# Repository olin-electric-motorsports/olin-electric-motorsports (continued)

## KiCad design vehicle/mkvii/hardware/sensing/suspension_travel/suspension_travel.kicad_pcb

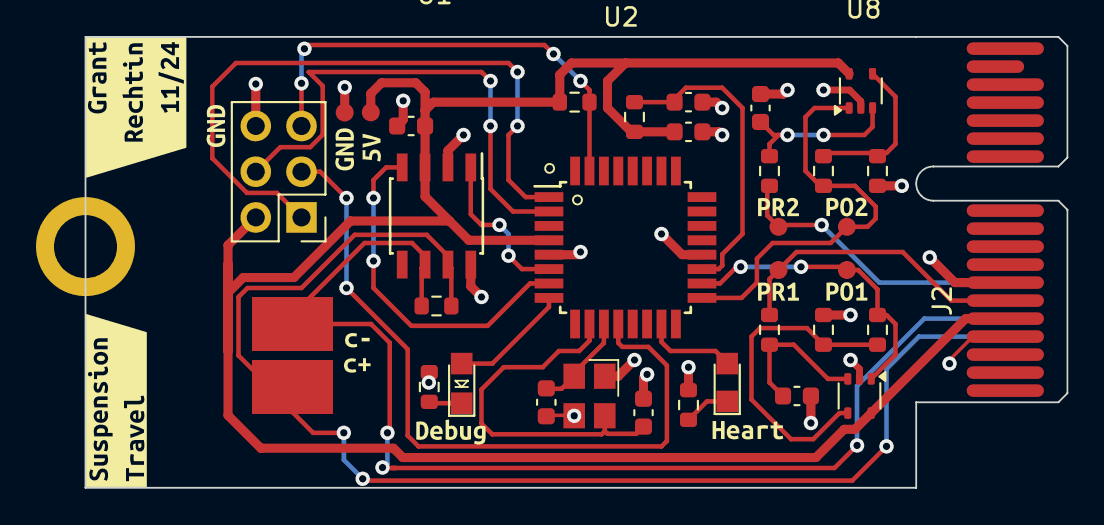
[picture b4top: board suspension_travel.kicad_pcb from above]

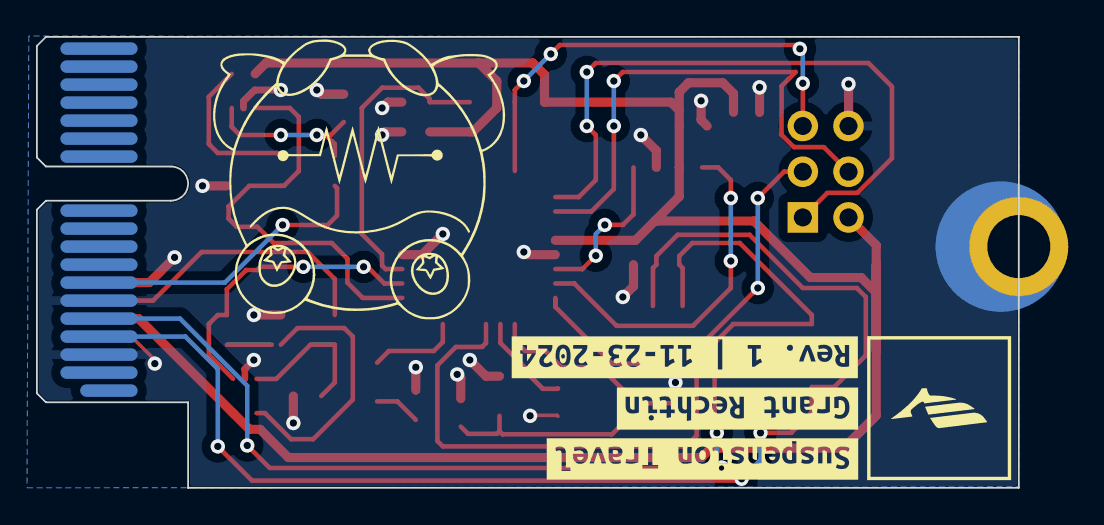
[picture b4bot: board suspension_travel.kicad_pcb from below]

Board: 2 copper layers, 54.6 x 25.0 mm, 52 parts (3 on the bottom side), 25 nets.

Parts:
5VTestPoint1: TestPoint; TestPoint_Pad_D1mm
C1, C3, C6, C7: C_0.1uF; C_0603
C2: C_100pF; C_0603
C4, C5: C_30pF; C_0603
Can+Tp1: TestPoint; Test_Point_SMD
Can-TP1: TestPoint; Test_Point_SMD
D1: LED_0805; LED_0805_OEM
D2: LED_AMBER; CHIPLED_0805
GND1: TestPoint; TestPoint_Pad_D1mm
H1: CONN_MountingHole; PCIe_Mount
J1: CONN_02X03; PinHeader_2x03_P2.54mm_Vertical
J2: CONN_pcie_x1; pcie_x1
LP1_POST1, LP1_PRE1, LP2_POST1, LP2_PRE1: TestPoint; TestPoint_Pad_D1mm
R1, R4, R5, R6, R9, R10: R_100; R_0603
R2: R_120_DNP; R_0603
R3: R_10K; R_0603
R7, R8: R_200; R_0603
R11: R_1K; R_0603
U1: MCP2561-E_SN; SOIC-8_3.9x4.9mm_Pitch1.27mm_OEM
U2: ATMEGA16M1; TQFP-32_7x7mm_Pitch0.8mm
U3, U8: U_OPAMP_MCP6001; SOT-353_SC-70-5
Y1: Crystal_SMD; Crystal_TXC7M
kibuzzard-673FD6A4: G***; kibuzzard-673FD6A4
kibuzzard-673FD6B3: G***; kibuzzard-673FD6B3
kibuzzard-673FD6DC: G***; kibuzzard-673FD6DC
kibuzzard-673FD6EA: G***; kibuzzard-673FD6EA
kibuzzard-673FD6F4: G***; kibuzzard-673FD6F4
kibuzzard-673FD70C: G***; kibuzzard-673FD70C
kibuzzard-673FD675, kibuzzard-673FD675#2: G***; kibuzzard-673FD675
kibuzzard-673FD704: G***; kibuzzard-673FD704
kibuzzard-673FD725: G***; kibuzzard-673FD725
kibuzzard-673FD744: G***; kibuzzard-673FD744
kibuzzard-6740EEA9: G***; kibuzzard-6740EEA9
kibuzzard-6740EF04: G***; kibuzzard-6740EF04
kibuzzard-674242B4: G***; kibuzzard-674242B4
kibuzzard-67424246: G***; kibuzzard-67424246
kibuzzard-67424290: G***; kibuzzard-67424290

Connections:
+5V: 5VTestPoint1.1, C1.1, C3.1, J1.2, J2.B5 (5V), R1.1, R3.1, U1.3 (VDD), U2.4 (VCC), U3.5 (V+), U8.5 (V+)
/CAN_+: Can+Tp1.1, J2.A4 (CAN+), R2.1, U1.7 (CANH)
/CAN_-: Can-TP1.1, J2.A5 (CAN-), R2.2, U1.6 (CANL)
/CAN_RX: U1.4 (RXD), U2.7 ((PCINT11/T1/ICP1B/RXCAN)PC3)
/CAN_TX: U1.1 (TXD), U2.6 ((PCINT10/T0/TXCAN)PC2)
/DEBUG_LED: D1.2 (A), U2.8 ((PCINT0/MISO/PSCOUT2A)PB0)
/Heartbeat: D2.2 (A), U2.15 ((PCINT23/ACMP0)PD7)
/MISO: J1.1, U2.1 ((PCINT18/PSCIN2/OC1A/MISO_A)PD2)
/MOSI: J1.4, U2.2 ((PCINT19/TXD/TXLIN/OC0A/~SS/MOSI_A)PD3)
/RESET: J1.5, R3.2, U2.31 ((PCINT24/OCD/~RESET)PE0)
/SCK: J1.3, U2.12 ((PCINT20/ADC1/RXD/RXLIN/ICP1A/SCK_A)PD4)
/lp1_Vout: J2.B6 (io_1), LP1_PRE1.1, R5.1
/lp1_fVout: LP1_POST1.1, R9.1, U2.18 ((PCINT13/ADC9/ACMP3/AMP1+)PC5), U3.1
/lp2_Vout: J2.A7 (io_2), LP2_PRE1.1, R6.1
/lp2_fVout: LP2_POST1.1, R10.1, U2.17 ((PCINT12/ADC8/ACMPN3/AMP1-)PC4), U8.1
GND: C1.2, C2.2, C3.2, C4.2, C5.2, C6.2, C7.2, GND1.1, H1.1, J1.6, J2.A3 (GND), J2.A6 (io_0), J2.B4 (GND), J2.B7 (io_3), R4.2, R7.1, R8.1, R11.2, U1.2 (VSS), U1.8 (STBY), U2.5 (GND), U2.20 (AGND), U3.2 (V-), U8.2 (V-), Y1.2, Y1.4
unnamed: D1.1 (K), R4.1
unnamed: D2.1 (K), R11.1
unnamed: C5.1, U2.10 ((PCINT25/OC0B/XTAL1)PE1), Y1.3
unnamed: C4.1, U2.11 ((PCINT26/ADC0/XTAL2)PE2), Y1.1
unnamed: C2.1, R1.2, U2.19 (AVCC)
unnamed: C6.1, R5.2, U3.3 (+)
unnamed: R7.2, R9.2, U3.4 (-)
unnamed: C7.1, R6.2, U8.3 (+)
unnamed: R8.2, R10.2, U8.4 (-)

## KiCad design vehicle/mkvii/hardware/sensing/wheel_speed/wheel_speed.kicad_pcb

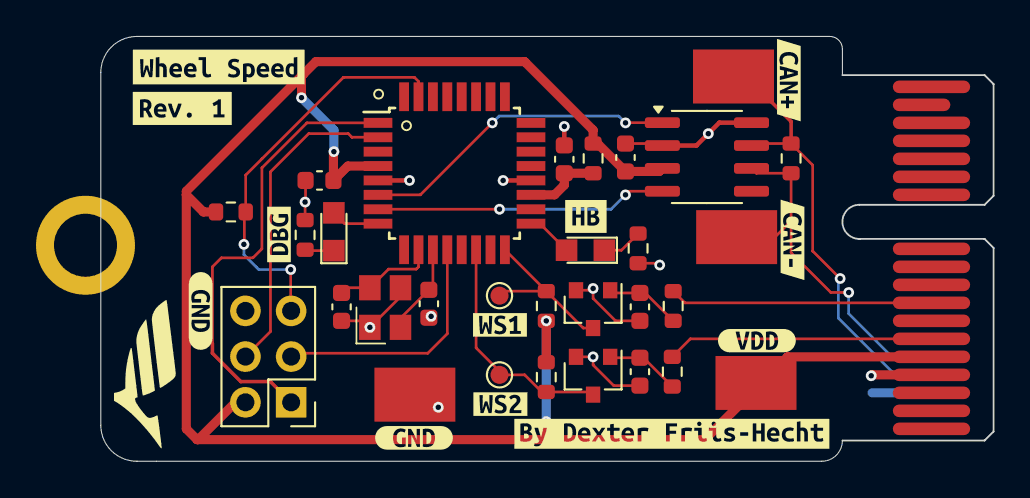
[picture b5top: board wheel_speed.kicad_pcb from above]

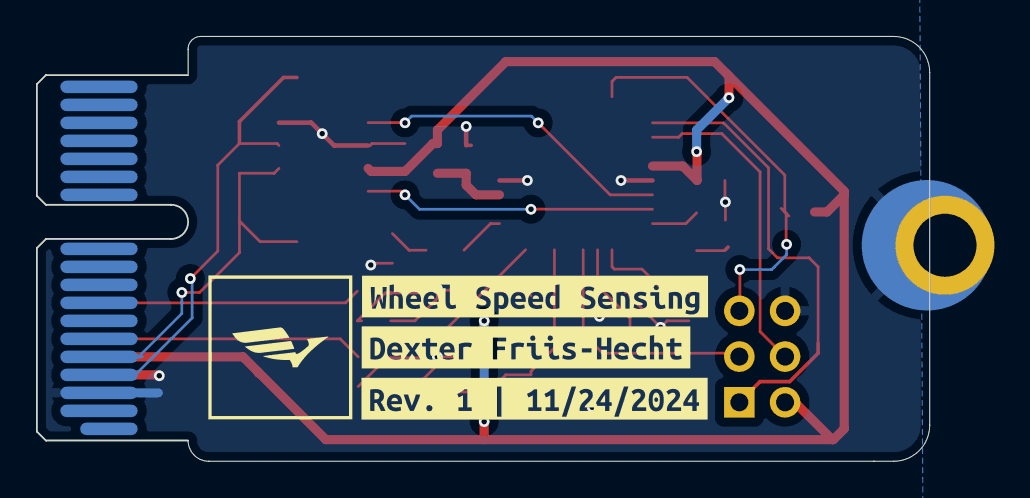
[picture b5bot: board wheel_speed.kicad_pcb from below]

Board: 2 copper layers, 49.6 x 23.6 mm, 46 parts (3 on the bottom side), 23 nets.

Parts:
C1: C_0.1uF; C_0603
C2: C_100pF; C_0603
C3: 0u1F; C_0603
C4, C5: C_30pF; C_0603
C6, C7: 10nF; C_0603
D1, D2: LED_BLUE; CHIPLED_0805
GND1: TestPoint; Test_Point_SMD
J1: CONN_02x03; PinHeader_2x03_P2.54mm_Vertical
J2: pcie_x1
Q1, Q2: SSM3K333R; SOT-23F
R1, R4, R9: R_100; R_0603
R2: R_120_DNP; R_0603
R3: R_10K; R_0603
R5, R7: 1K; R_0603
R6, R8: R_1K_DNP; R_0603
TP1, TP2: TP_SMD; Test_Point_SMD
U1: ATMEGA16M1; TQFP-32_7x7mm_Pitch0.8mm
U2: MCP2561-E-SN; SOIC-8_3.9x4.9mm_P1.27mm
VDD1: TestPoint; Test_Point_SMD
WS1, WS2: TestPoint; TestPoint_Pad_D1.0mm
Y1: Crystal_16MHz_18pF; Crystal_TXC7M
kibuzzard-67434E9E: G***; kibuzzard-67434E9E
kibuzzard-67434EBC: G***; kibuzzard-67434EBC
kibuzzard-67434F1A: G***; kibuzzard-67434F1A
kibuzzard-674365BB: G***; kibuzzard-674365BB
kibuzzard-674365C6: G***; kibuzzard-674365C6
kibuzzard-674365DE: G***; kibuzzard-674365DE
kibuzzard-6743680D: G***; kibuzzard-6743680D
kibuzzard-6743681C: G***; kibuzzard-6743681C
kibuzzard-6743683A: G***; kibuzzard-6743683A
kibuzzard-67436823: G***; kibuzzard-67436823
kibuzzard-67436829: G***; kibuzzard-67436829
kibuzzard-67436831: G***; kibuzzard-67436831
kibuzzard-67436866: G***; kibuzzard-67436866
kibuzzard-67436872: G***; kibuzzard-67436872
kibuzzard-67436973: G***; kibuzzard-67436973

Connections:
+5V: C1.1, C3.2, J1.2, J2.B5 (5V), R1.1, R3.2, R6.1, R8.1, U1.4 (VCC), U2.3 (VDD), VDD1.1
/CAN_+: J2.A4 (CAN+), R2.1, TP2.1, U2.7 (CANH)
/CAN_-: J2.A5 (CAN-), R2.2, TP1.1, U2.6 (CANL)
/CAN_RX: U1.7 ((PCINT11/T1/ICP1B/RXCAN)PC3), U2.4 (RXD)
/CAN_TX: U1.6 ((PCINT10/T0/TXCAN)PC2), U2.1 (TXD)
/DEBUG_LED: D1.2 (A), U1.8 ((PCINT0/MISO/PSCOUT2A)PB0)
/HEARTBEAT_LED: D2.2 (A), U1.17 ((PCINT12/ADC8/ACMPN3/AMP1-)PC4)
/MISO: J1.1, U1.1 ((PCINT18/PSCIN2/OC1A/MISO_A)PD2)
/MOSI: J1.4, U1.2 ((PCINT19/TXD/TXLIN/OC0A/~SS/MOSI_A)PD3)
/RESET: J1.5, R3.1, U1.31 ((PCINT24/OCD/~RESET)PE0)
/SCK: J1.3, U1.12 ((PCINT20/ADC1/RXD/RXLIN/ICP1A/SCK_A)PD4)
/ws1_Vout: J2.B8 (io_5), R7.1
/ws1_fVout: Q1.3 (D), R8.2, U1.16 ((PCINT2/ADC5/INT1/ACMPN0)PB2), WS1.1
/ws2_Vout: J2.B6 (io_1), R5.1
/ws2_fVout: Q2.3 (D), R6.2, U1.14 ((PCINT22/ADC3/INT0/ACMPN2)PD6), WS2.1
GND: C1.2, C2.2, C3.1, C4.2, C5.2, C6.2, C7.2, GND1.1, J1.6, J2.A3 (GND), J2.B4 (GND), Q1.2 (S), Q2.2 (S), R4.2, R9.2, U1.5 (GND), U1.20 (AGND), U2.2 (VSS), U2.8 (STBY), Y1.2, Y1.4
unnamed: D1.1 (K), R4.1
unnamed: D2.1 (K), R9.1
unnamed: C6.1, Q1.1 (G), R7.2
unnamed: C7.1, Q2.1 (G), R5.2
unnamed: C5.1, U1.10 ((PCINT25/OC0B/XTAL1)PE1), Y1.3
unnamed: C4.1, U1.11 ((PCINT26/ADC0/XTAL2)PE2), Y1.1
unnamed: C2.1, R1.2, U1.19 (AVCC)

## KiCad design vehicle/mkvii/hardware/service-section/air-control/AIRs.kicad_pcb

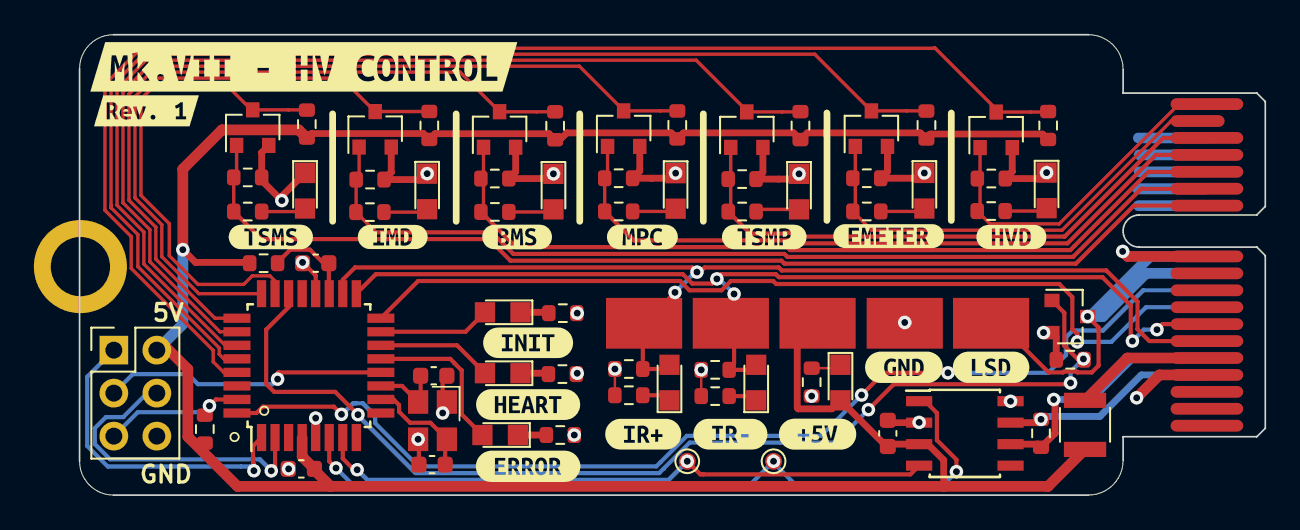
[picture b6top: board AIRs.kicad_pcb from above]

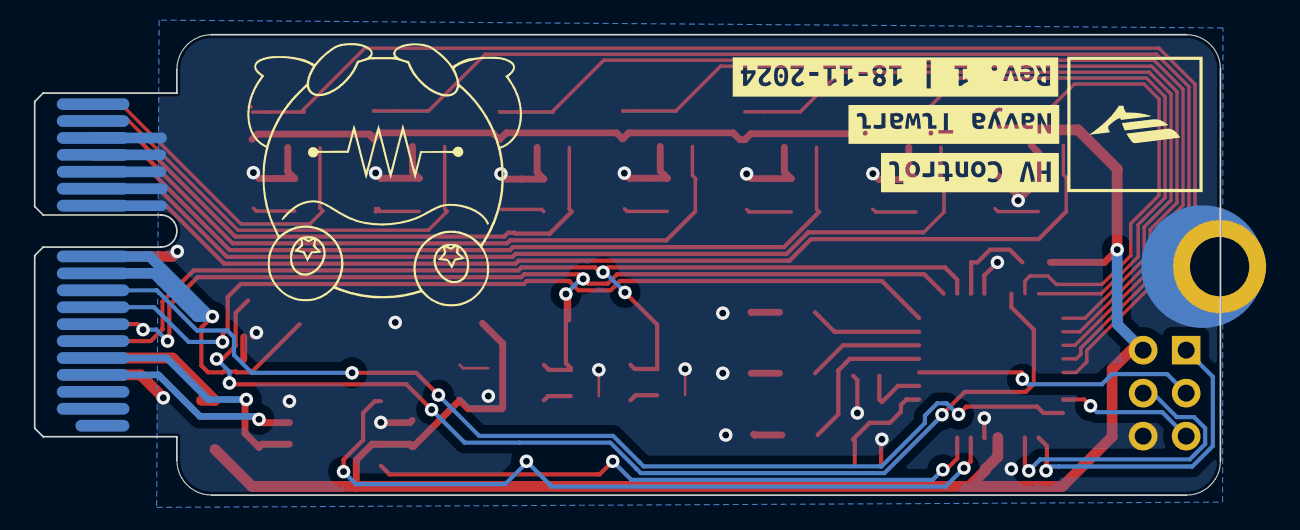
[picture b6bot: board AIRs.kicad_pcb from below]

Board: 2 copper layers, 70.0 x 27.2 mm, 93 parts (3 on the bottom side), 50 nets.

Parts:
C1, C7: 0.1uF; C_0603
C2: C_100pF; C_0603
C3, C4: C_30pF; C_0603
D1, D15: LED_AMBER; CHIPLED_0805
D2: HEARTBEAT; CHIPLED_0805
D3: ERROR; CHIPLED_0805
D4, D5, D6, D7, D8, D9, D10: LED_BLUE; CHIPLED_0805
D11: INIT; CHIPLED_0805
D14: LED_WHITE; CHIPLED_0805
F1: F_500mA_16V; Fuse_1210
H1: CONN_MountingHole; PCIe_Mount
J2: CONN_02x03; PinHeader_2x03_P2.54mm_Vertical
J3: CONN_pcie_x1; pcie_x1
Q2, Q3, Q4, Q5, Q6, Q7, Q8, Q9: SSM3K333R; SOT-23F
R1: R_100; R_0603
R4, R5, R8, R14, R17, R20, R23, R26, R29, R34: R_10K; R_0603
R6, R7, R9, R10, R11, R33, R283: 1KR; R_0603
R12, R15, R18, R21, R24, R27, R31: R_100K; R_0603
R13, R16, R19, R22, R25, R28, R32: 3KR; R_0603
R30: R_120_DNP; R_0603
TP1, TP2, TP5, TP6, TP7: Test_Point_SMD
TP3, TP4: Test_Point_SMD; TestPoint_Pad_D1.0mm
U1: ATMEGA16M1; TQFP-32_7x7mm_Pitch0.8mm
U2: MAX33011EASA; SOIC-8_3.9x4.9mm_Pitch1.27mm_OEM
Y1: Crystal_16MHz_18pF; Crystal_TXC7M
kibuzzard-673ABF3D: G***; kibuzzard-673ABF3D
kibuzzard-673ABF10: G***; kibuzzard-673ABF10
kibuzzard-673AC5AC: G***; kibuzzard-673AC5AC
kibuzzard-673AC09F: G***; kibuzzard-673AC09F
kibuzzard-673AC47D: G***; kibuzzard-673AC47D
kibuzzard-673AC56E: G***; kibuzzard-673AC56E
kibuzzard-673AC077: G***; kibuzzard-673AC077
kibuzzard-673AC097: G***; kibuzzard-673AC097
kibuzzard-673ACD4F: G***; kibuzzard-673ACD4F
kibuzzard-673ACD76: G***; kibuzzard-673ACD76
kibuzzard-673ACE7D: G***; kibuzzard-673ACE7D
kibuzzard-673ACEAB: G***; kibuzzard-673ACEAB
kibuzzard-673ACEB4: G***; kibuzzard-673ACEB4
kibuzzard-673ACEBD: G***; kibuzzard-673ACEBD
kibuzzard-673ACEC4: G***; kibuzzard-673ACEC4
kibuzzard-673ACECD: G***; kibuzzard-673ACECD
kibuzzard-673ACED7: G***; kibuzzard-673ACED7
kibuzzard-673AD1C7: G***; kibuzzard-673AD1C7
kibuzzard-673AD187: G***; kibuzzard-673AD187
kibuzzard-673AD216: G***; kibuzzard-673AD216

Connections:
+5V: C1.1, C7.1, D14.2 (A), F1.1, J2.2, R1.1, R4.2, R5.1, R14.1, R17.1, R20.1, R23.1, R26.1, R29.1, TP1.1, U1.4 (VCC), U2.3 (VDD)
/AIR+_LSD_OUT: J3.A10 (io_8), J3.A11 (io_10), Q9.3 (D), TP7.1
/AIR+_WELD_DETECT_IN: D1.2 (A), J3.B6 (io_1), R8.1, TP5.1, U1.18 ((PCINT13/ADC9/ACMP3/AMP1+)PC5)
/AIR-_LSD: Q9.1 (G), R11.2, U1.22 ((PCINT14/ADC10/ACMP1)PC6)
/AIR-_WELD_DETECT_IN: D15.2 (A), J3.B7 (io_3), R34.1, TP2.1, U1.17 ((PCINT12/ADC8/ACMPN3/AMP1-)PC4)
/CAN +: J3.A4 (CAN+), R30.1, U2.7 (CANH)
/CAN -: J3.A5 (CAN-), R30.2, U2.6 (CANL)
/CAN Tcvr./CAN RX: TP4.1, U1.7 ((PCINT11/T1/ICP1B/RXCAN)PC3), U2.4 (RXD)
/CAN Tcvr./CAN TX: TP3.1, U1.6 ((PCINT10/T0/TXCAN)PC2), U2.1 (TXD)
/ERROR: D3.2 (A), U1.13 ((PCINT21/ADC2/ACMP2)PD5)
/HEARTBEAT: D2.2 (A), U1.14 ((PCINT22/ADC3/INT0/ACMPN2)PD6)
/IMD_SENSE: J3.A9 (io_6), U1.32 ((PCINT17/CLKO/PSCIN0)PD1)
/INIT: D11.2 (A), U1.15 ((PCINT23/ACMP0)PD7)
/MISO: J2.1, U1.1 ((PCINT18/PSCIN2/OC1A/MISO_A)PD2)
/MOSI: J2.4, U1.2 ((PCINT19/TXD/TXLIN/OC0A/~SS/MOSI_A)PD3)
/PRECHARGE: J3.A8 (io_4), U1.16 ((PCINT2/ADC5/INT1/ACMPN0)PB2)
/RESET: J2.5, R4.1, U1.31 ((PCINT24/OCD/~RESET)PE0)
/SCK: J2.3, U1.12 ((PCINT20/ADC1/RXD/RXLIN/ICP1A/SCK_A)PD4)
/SHDN_SENSE_BMS: J3.B14 (io_17), Q4.1 (G), R18.1, R19.1
/SHDN_SENSE_BMS_OUT: Q4.3 (D), R17.2, U1.25 ((PCINT15/D2A/AMP2+)PC7)
/SHDN_SENSE_EMETER: J3.B17 (SHDN_OUT/io_23), Q7.1 (G), R27.1, R28.1
/SHDN_SENSE_EMETER_OUT: Q7.3 (D), R26.2, U1.28 ((PCINT7/ADC4/SCK/PSCOUT0B)PB7)
/SHDN_SENSE_HVD: J3.B18 (SHDN_OUT/io_25), Q8.1 (G), R31.1, R32.1
/SHDN_SENSE_HVD_OUT: Q8.3 (D), R29.2, U1.29 ((PCINT16/PSCOUT0A)PD0)
/SHDN_SENSE_IMD: J3.B13 (io_15), Q5.1 (G), R21.1, R22.1
/SHDN_SENSE_IMD_OUT: Q5.3 (D), R20.2, U1.24 ((PCINT4/AMP0+)PB4)
/SHDN_SENSE_MPC: J3.B15 (io_19), Q3.1 (G), R15.1, R16.1
/SHDN_SENSE_MPC_OUT: Q3.3 (D), R14.2, U1.26 ((PCINT5/ADC6/INT2/ACMPN1/AMP2-)PB5)
/SHDN_SENSE_TSMP: J3.B16 (io_21), Q2.1 (G), R12.1, R13.1
/SHDN_SENSE_TSMP_OUT: Q2.3 (D), R5.2, U1.27 ((PCINT6/ADC7/PSCOUT1B)PB6)
/SHDN_SENSE_TSMS: J3.B12 (io_13), Q6.1 (G), R24.1, R25.1
/SHDN_SENSE_TSMS_OUT: Q6.3 (D), R23.2, U1.23 ((PCINT3/AMP0-)PB3)
GND: C1.2, C2.2, C3.2, C4.2, C7.2, D4.1 (K), D5.1 (K), D6.1 (K), D7.1 (K), D8.1 (K), D9.1 (K), D10.1 (K), H1.1, J2.6, J3.A12 (io_12), J3.A13 (io_14), J3.A14 (io_16), J3.A15 (io_18), J3.A16 (io_20), J3.B4 (GND), J3.B11 (io_11), Q2.2 (S), Q3.2 (S), Q4.2 (S), Q5.2 (S), Q6.2 (S), Q7.2 (S), Q8.2 (S), Q9.2 (S), R6.1, R7.2, R8.2, R9.2, R10.2, R11.1, R12.2, R15.2, R18.2, R21.2, R24.2, R27.2, R31.2, R33.1, R34.2, R283.1, TP6.1, U1.5 (GND), U1.20 (AGND), U2.2 (VSS), U2.8 (STBY), Y1.2, Y1.4
unnamed: D1.1 (K), R6.2
unnamed: D2.1 (K), R10.1
unnamed: D3.1 (K), R7.1
unnamed: D4.2 (A), R13.2
unnamed: D5.2 (A), R16.2
unnamed: D6.2 (A), R19.2
unnamed: D7.2 (A), R22.2
unnamed: D8.2 (A), R25.2
unnamed: D9.2 (A), R28.2
unnamed: D10.2 (A), R32.2
unnamed: D11.1 (K), R9.1
unnamed: D14.1 (K), R283.2
unnamed: D15.1 (K), R33.2
unnamed: F1.2, J3.B5 (5V)
unnamed: C4.1, U1.10 ((PCINT25/OC0B/XTAL1)PE1), Y1.3
unnamed: C3.1, U1.11 ((PCINT26/ADC0/XTAL2)PE2), Y1.1
unnamed: C2.1, R1.2, U1.19 (AVCC)

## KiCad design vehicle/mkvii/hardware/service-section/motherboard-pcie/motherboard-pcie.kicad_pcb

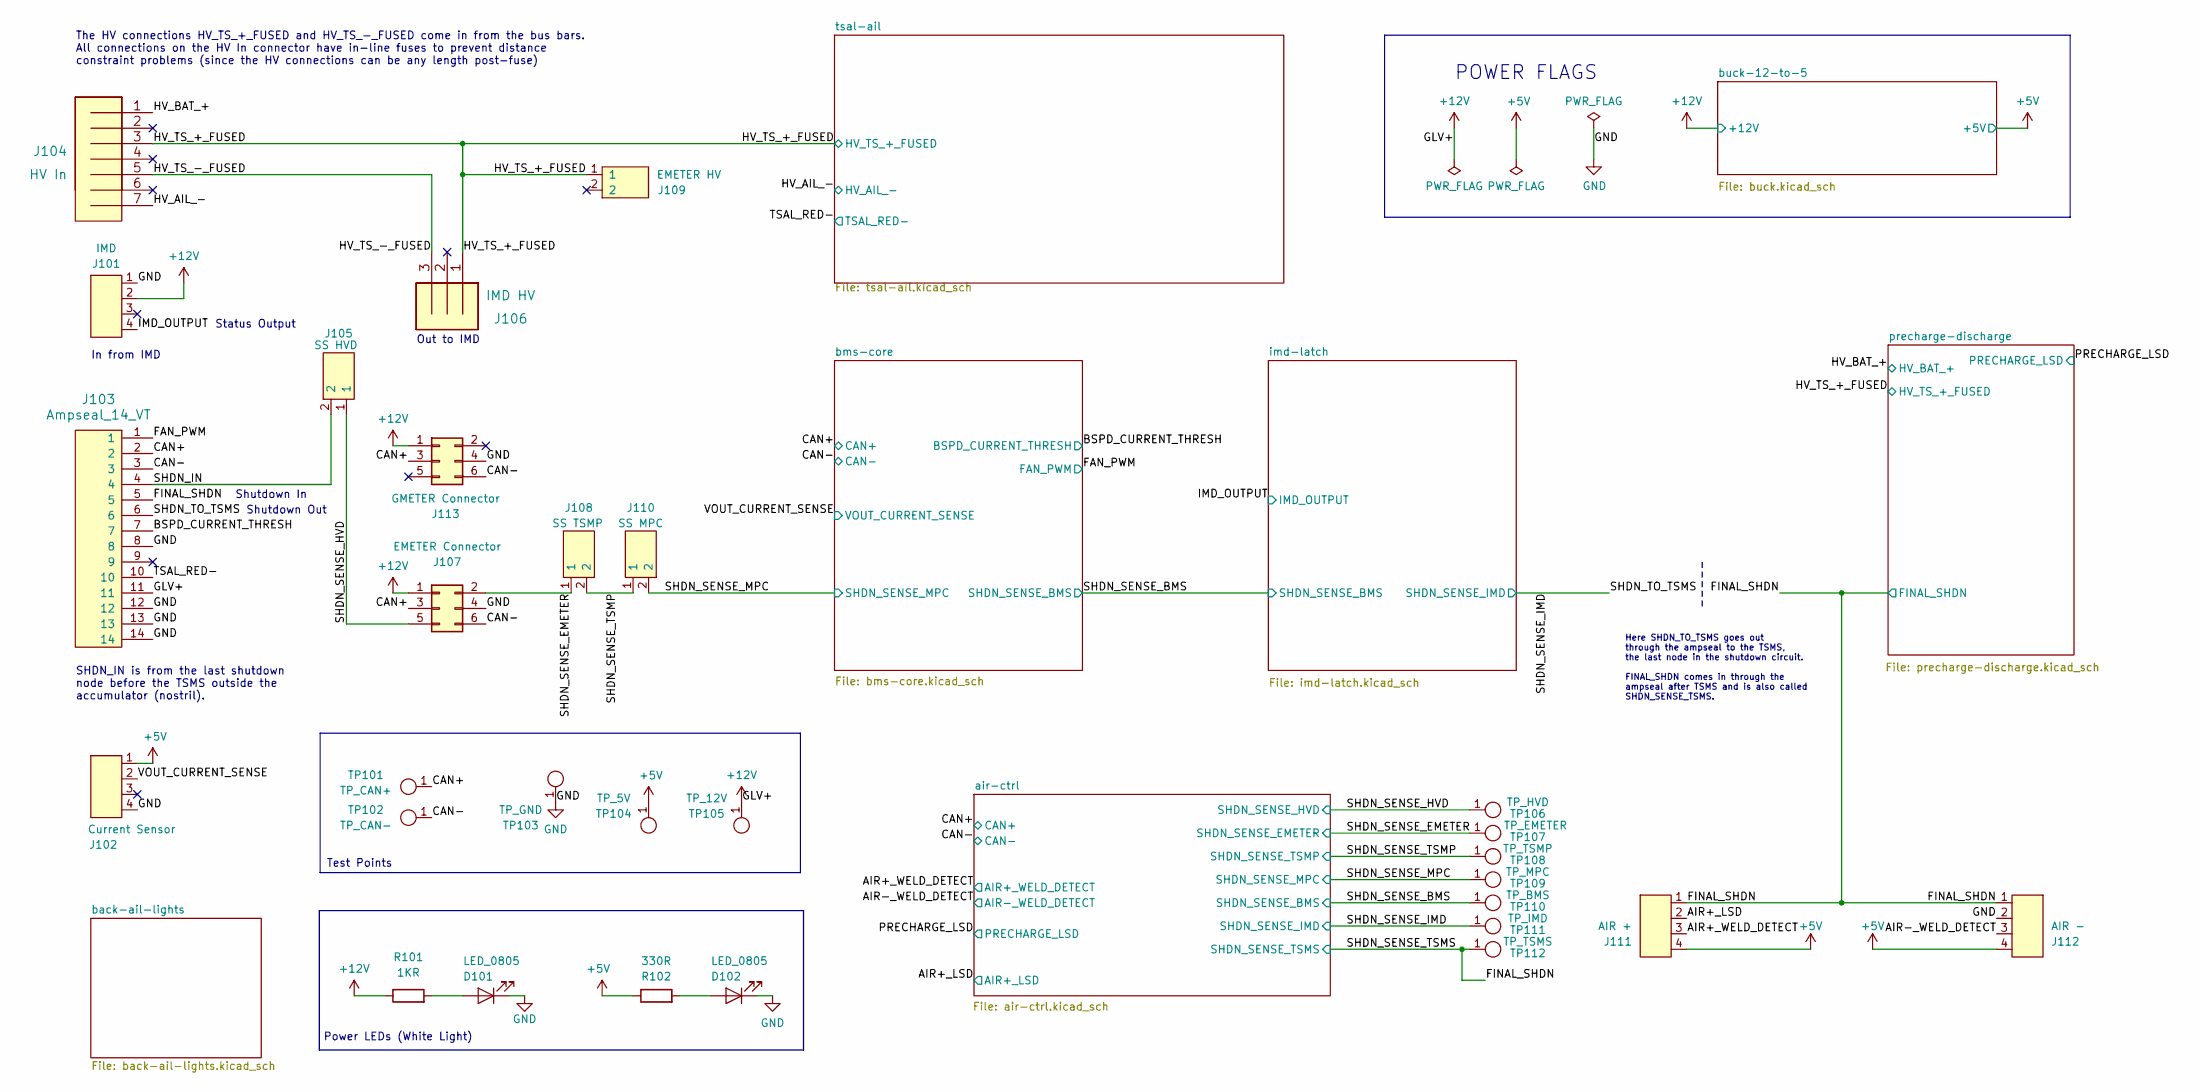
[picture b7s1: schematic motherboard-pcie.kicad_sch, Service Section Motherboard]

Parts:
D101, D102: LED_0805; LED_0805_OEM; MPN 475-1410-1-ND
J101: IMD; MicroFit_VT_4; MPN 430450414
J102: Current Sensor; MicroFit_VT_4; MPN 430450414
J103: Ampseal_14_VT; Ampseal_14; MPN 1-776261-1
J104: HV In; MicroFit_VT_7; MPN 436500727
J105: SS HVD; MicroFit_V_2; MPN WM10660-ND
J106: IMD HV; MicroFit_VT_3; MPN 436500327
J107: EMETER Connector; Molex_Micro-Fit_3.0_43045-0612_2x03_P3.00mm_Vertical
J108: SS TSMP; MicroFit_V_2; MPN WM10660-ND
J109: EMETER HV; MicroFit_V_2; MPN WM10660-ND
J110: SS MPC; MicroFit_V_2; MPN WM10660-ND
J111: AIR +; MicroFit_VT_4; MPN 430450414
J112: AIR -; MicroFit_VT_4; MPN 430450414
J113: GMETER Connector; Molex_Micro-Fit_3.0_43045-0612_2x03_P3.00mm_Vertical
R101: 1KR; R_0603; MPN RMCF0603FT1K00
R102: 330R; R_0603; MPN WR06X3300FTL
TP101: TP_CAN+; Test_Point_SMD; MPN 5019
TP102: TP_CAN-; Test_Point_SMD; MPN 5019
TP103: TP_GND; Test_Point_SMD; MPN 5019
TP104: TP_5V; Test_Point_SMD; MPN 5019
TP105: TP_12V; Test_Point_SMD; MPN 5019
TP106: TP_HVD; Test_Point_SMD; MPN 5019
TP107: TP_EMETER; Test_Point_SMD; MPN 5019
TP108: TP_TSMP; Test_Point_SMD; MPN 5019
TP109: TP_MPC; Test_Point_SMD; MPN 5019
TP110: TP_BMS; Test_Point_SMD; MPN 5019
TP111: TP_IMD; Test_Point_SMD; MPN 5019
TP112: TP_TSMS; Test_Point_SMD; MPN 5019

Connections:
+5V: J102.1, J111.4, J112.4, R102.1, TP104.1; also elsewhere on the board
+12V: J101.2, J103.11, J107.1, J113.1, R101.1, TP105.1; also elsewhere on the board
/AIR+_LSD: J111.2; also elsewhere on the board
/AIR+_WELD_DETECT: J111.3; also elsewhere on the board
/AIR-_WELD_DETECT: J112.3; also elsewhere on the board
/BSPD_CURRENT_THRESH: J103.7; also elsewhere on the board
/CAN+: J103.2, J107.3, J113.3, TP101.1; also elsewhere on the board
/CAN-: J103.3, J107.6, J113.6, TP102.1; also elsewhere on the board
/FAN_PWM: J103.1; also elsewhere on the board
/FINAL_SHDN: J103.5, J111.1, J112.1, TP112.1; also elsewhere on the board
/HV_AIL_-: J104.7; also elsewhere on the board
/HV_BAT_+: J104.1; also elsewhere on the board
/HV_TS_+_FUSED: J104.3, J106.1, J109.1; also elsewhere on the board
/HV_TS_-_FUSED: J104.5, J106.3
/IMD_OUTPUT: J101.4; also elsewhere on the board
/SHDN_IN: J103.4, J105.2
/SHDN_SENSE_BMS: TP110.1; also elsewhere on the board
/SHDN_SENSE_EMETER: J107.2, J108.1, TP107.1; also elsewhere on the board
/SHDN_SENSE_HVD: J105.1, J107.5, TP106.1; also elsewhere on the board
/SHDN_SENSE_IMD: J103.6, TP111.1; also elsewhere on the board
/SHDN_SENSE_MPC: J110.2, TP109.1; also elsewhere on the board
/SHDN_SENSE_TSMP: J108.2, J110.1, TP108.1; also elsewhere on the board
/TSAL_RED-: J103.10; also elsewhere on the board
/VOUT_CURRENT_SENSE: J102.2; also elsewhere on the board
GND: D101.1 (K), D102.1 (K), J101.1, J102.4, J103.8, J103.12, J103.13, J103.14, J107.4, J112.2, J113.4, TP103.1; also elsewhere on the board
unnamed: D101.2 (A), R101.2
unnamed: D102.2 (A), R102.2

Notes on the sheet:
SHDN_IN is from the last shutdown node before the TSMS outside the accumulator (nostril).
Shutdown Out
Test Points
Shutdown In
Status Output
Here SHDN_TO_TSMS goes out through the ampseal to the TSMS, the last node in the shutdown circuit. FINAL_SHDN comes in through the ampseal after TSMS and is also called SHDN_SENSE_TSMS.
Power LEDs (White Light)
POWER FLAGS
Out to IMD
In from IMD
The HV connections HV_TS_+_FUSED and HV_TS_-_FUSED come in from the bus bars. All connections on the HV In connector have in-line fuses to prevent distance constraint problems (since the HV connections can be any length post-fuse)

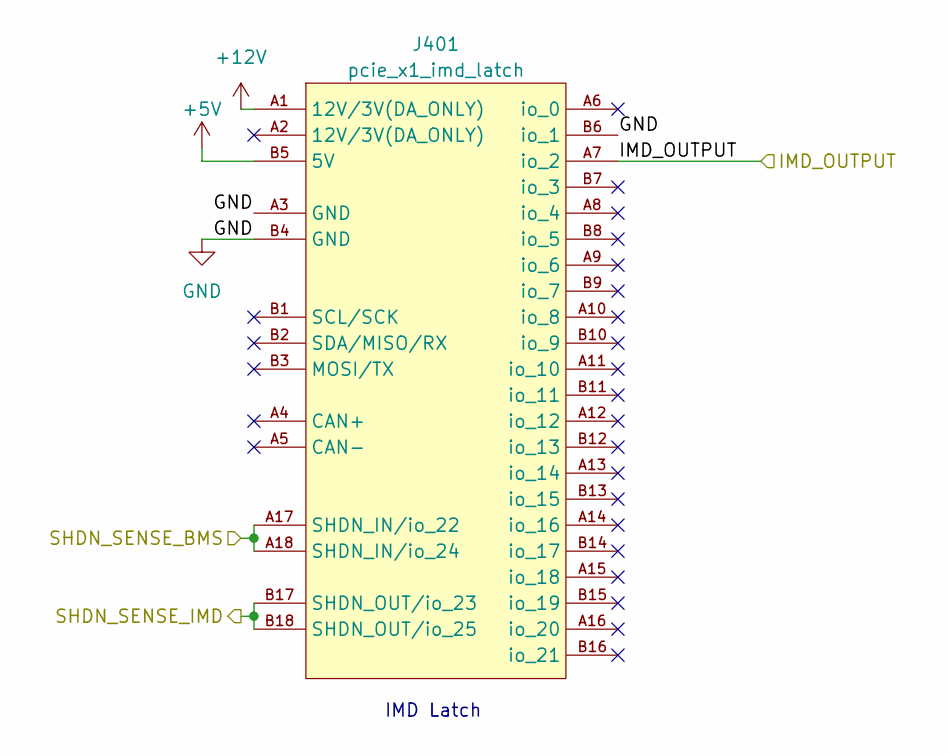
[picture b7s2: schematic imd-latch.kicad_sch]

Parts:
J401: pcie_x1_imd_latch; te_pcie_x1_connector

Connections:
+5V: J401.B5 (5V); also elsewhere on the board
+12V: J401.A1 (12V/3V(DA_ONLY)); also elsewhere on the board
/IMD_OUTPUT: J401.A7 (io_2); also elsewhere on the board
/SHDN_SENSE_BMS: J401.A17 (SHDN_IN/io_22), J401.A18 (SHDN_IN/io_24); also elsewhere on the board
/SHDN_SENSE_IMD: J401.B17 (SHDN_OUT/io_23), J401.B18 (SHDN_OUT/io_25); also elsewhere on the board
GND: J401.A3 (GND), J401.B4 (GND), J401.B6 (io_1); also elsewhere on the board

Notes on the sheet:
IMD Latch

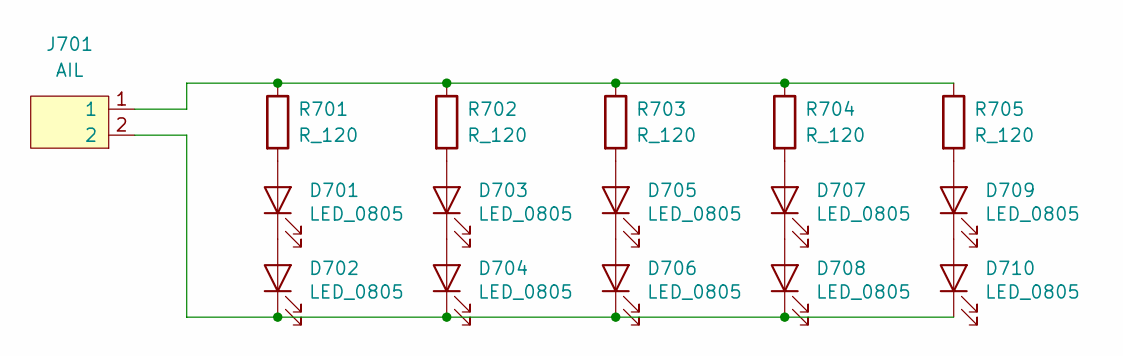
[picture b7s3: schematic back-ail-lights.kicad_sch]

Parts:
D701, D702, D703, D704, D705, D706, D707, D708, D709, D710: LED_0805; LED_0805_OEM_no_border; MPN 475-1410-1-ND
J701: AIL; MicroFit_V_2; MPN WM10660-ND
R701, R702, R703, R704, R705: R_120; R_0805_OEM; MPN 667-ERJ-6ENF1200V

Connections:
unnamed: D701.2 (A), R701.2
unnamed: D701.1 (K), D702.2 (A)
unnamed: D702.1 (K), D704.1 (K), D706.1 (K), D708.1 (K), D710.1 (K), J701.2
unnamed: D703.2 (A), R702.2
unnamed: D703.1 (K), D704.2 (A)
unnamed: D705.2 (A), R703.2
unnamed: D705.1 (K), D706.2 (A)
unnamed: D707.1 (K), D708.2 (A)
unnamed: D707.2 (A), R704.2
unnamed: D709.1 (K), D710.2 (A)
unnamed: D709.2 (A), R705.2
unnamed: J701.1, R701.1, R702.1, R703.1, R704.1, R705.1

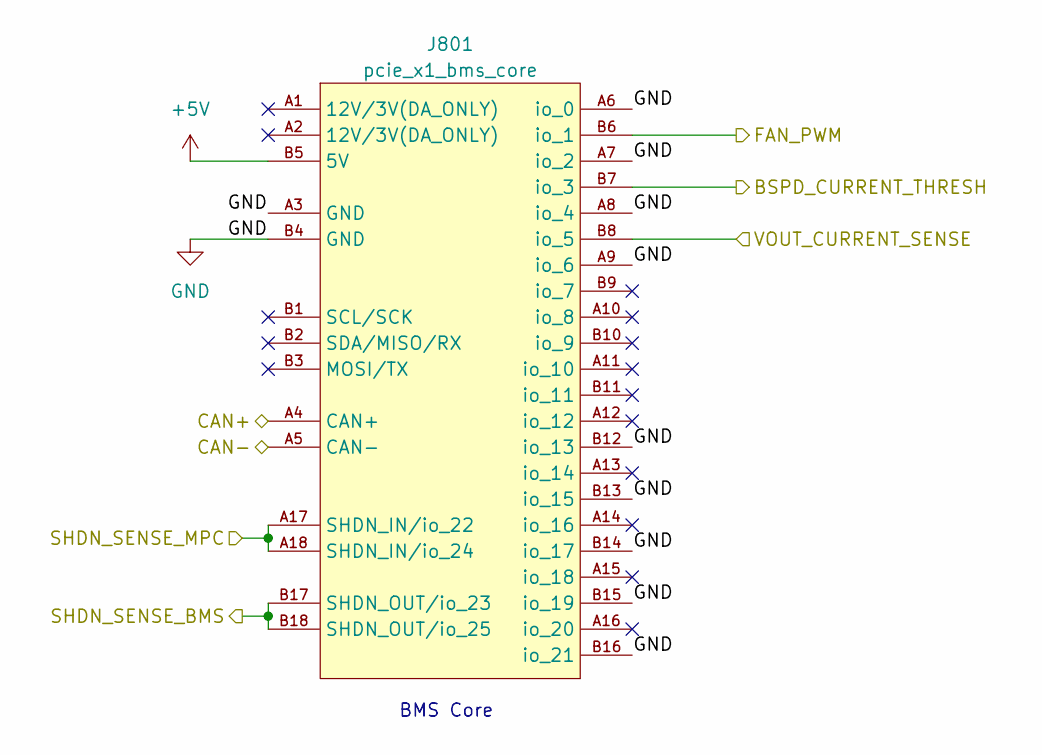
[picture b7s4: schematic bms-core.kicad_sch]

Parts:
J801: pcie_x1_bms_core; te_pcie_x1_connector

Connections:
+5V: J801.B5 (5V); also elsewhere on the board
/BSPD_CURRENT_THRESH: J801.B7 (io_3); also elsewhere on the board
/CAN+: J801.A4 (CAN+); also elsewhere on the board
/CAN-: J801.A5 (CAN-); also elsewhere on the board
/FAN_PWM: J801.B6 (io_1); also elsewhere on the board
/SHDN_SENSE_BMS: J801.B17 (SHDN_OUT/io_23), J801.B18 (SHDN_OUT/io_25); also elsewhere on the board
/SHDN_SENSE_MPC: J801.A17 (SHDN_IN/io_22), J801.A18 (SHDN_IN/io_24); also elsewhere on the board
/VOUT_CURRENT_SENSE: J801.B8 (io_5); also elsewhere on the board
GND: J801.A3 (GND), J801.A6 (io_0), J801.A7 (io_2), J801.A8 (io_4), J801.A9 (io_6), J801.B4 (GND), J801.B12 (io_13), J801.B13 (io_15), J801.B14 (io_17), J801.B15 (io_19), J801.B16 (io_21); also elsewhere on the board

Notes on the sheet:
BMS Core

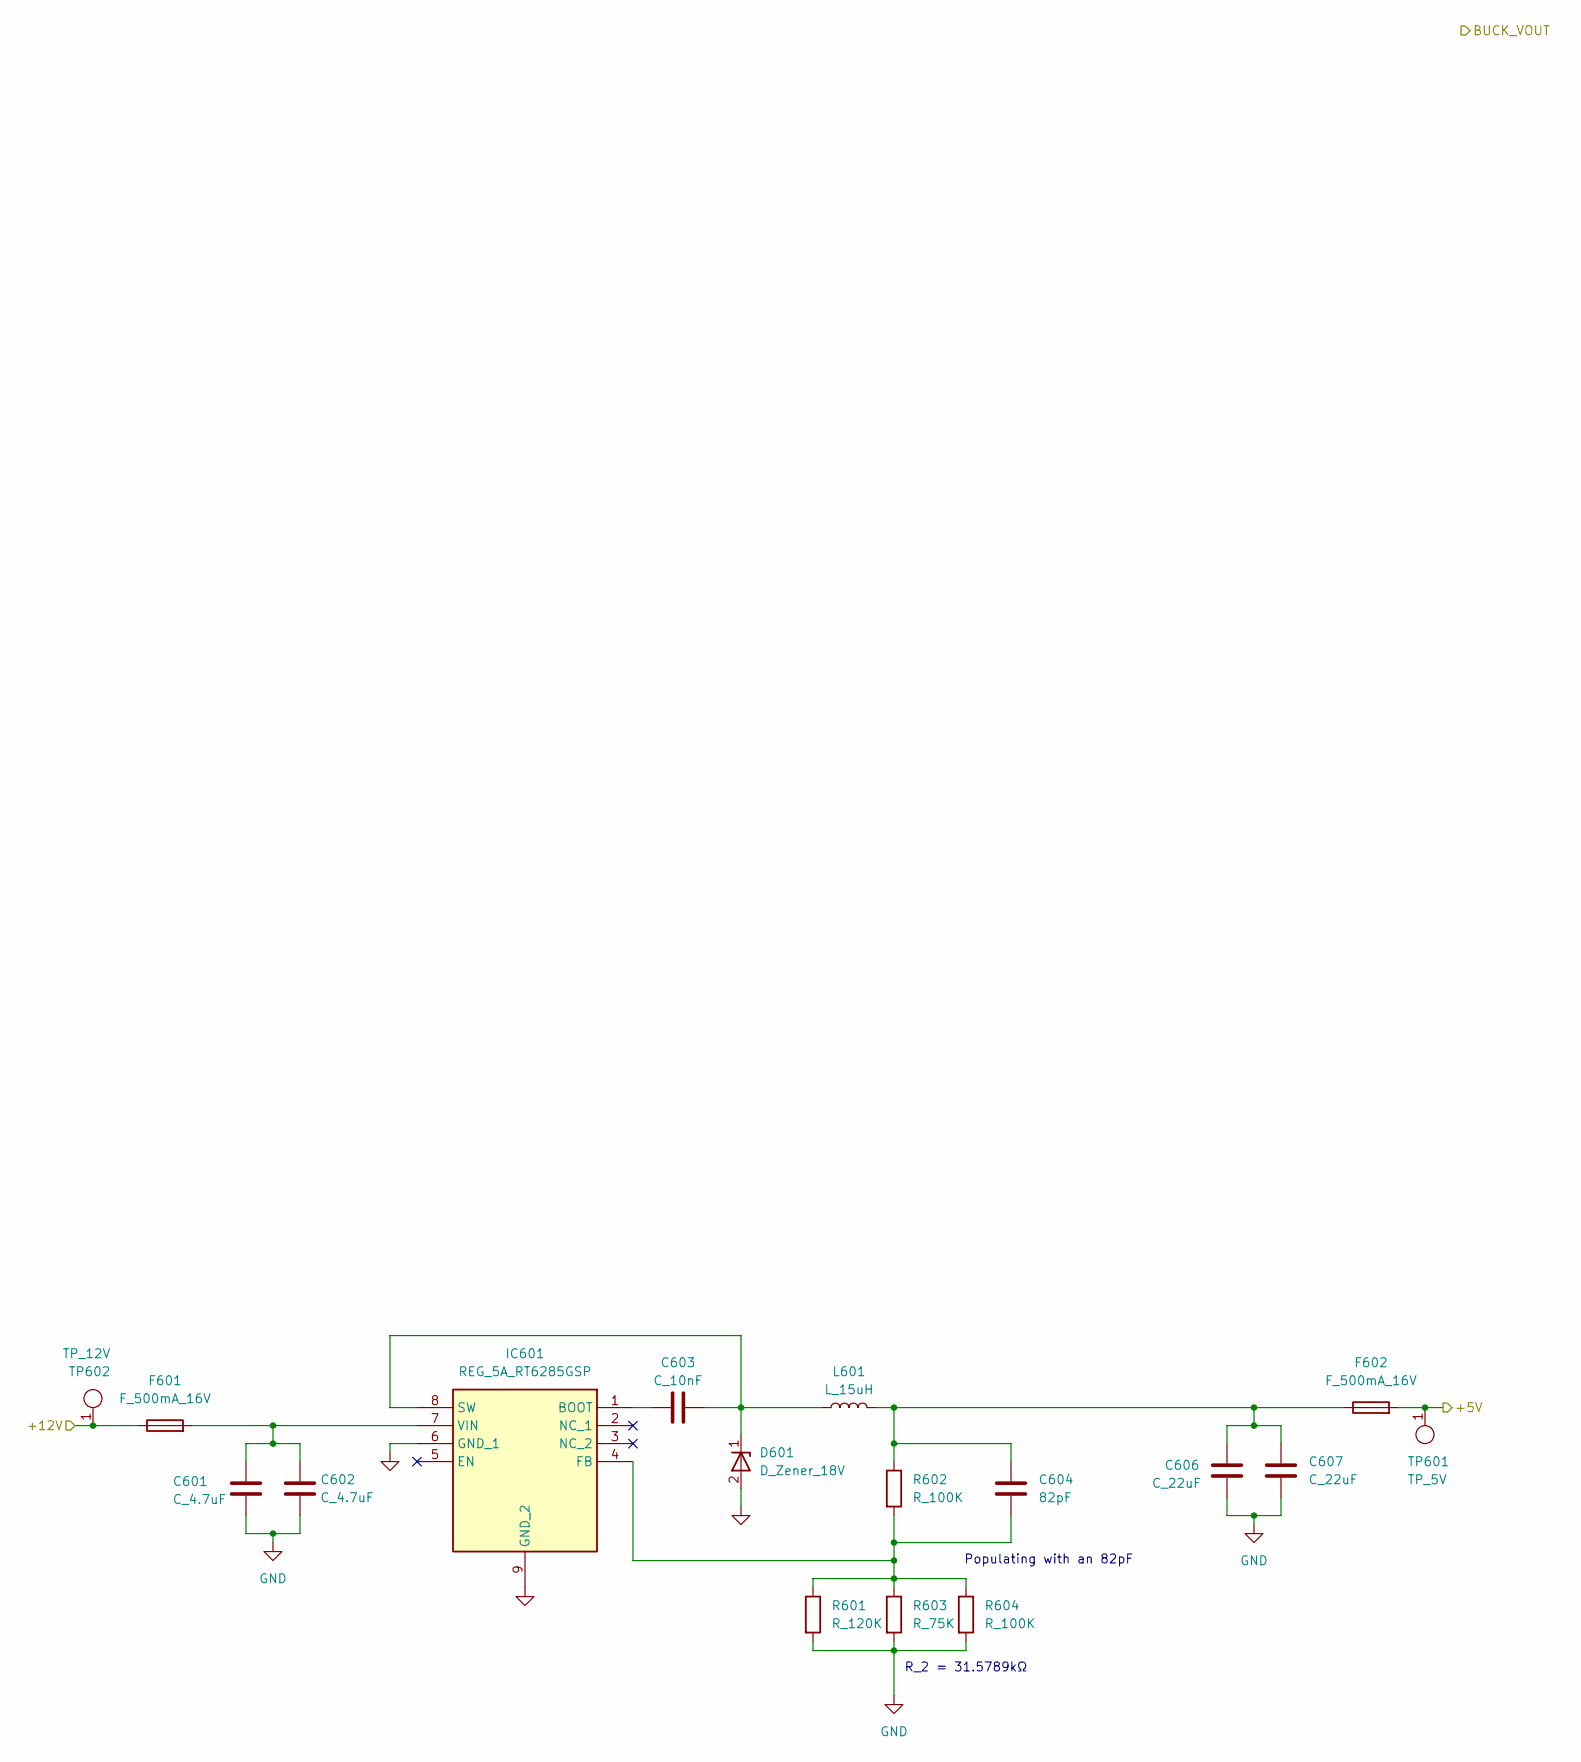
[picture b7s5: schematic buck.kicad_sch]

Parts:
C601, C602: C_4.7uF; C_0603; MPN GRT188R61E475ME13D
C603: C_10nF; C_0603; MPN CL10B103KB8NNNC
C604: 82pF; C_0603; MPN 0603N101F101CT
C606, C607: C_22uF; C_1206_3216Metric; MPN CL31A226KAHNNNE
D601: D_Zener_18V; DO-214AA; MPN SMBJ5355B-TP
F601, F602: F_500mA_16V; Fuse_1210; MPN 0ZCH0050FF2G
IC601: REG_5A_RT6285GSP; SOIC127P600X175-9N; Mouser Part Number 835-RT6285GSP
L601: L_15uH; NR10050T150M; MPN NR10050T150M
R601: R_120K; R_0603; MPN RC0603FR-13120KL
R602, R604: R_100K; R_0603; MPN RMCF0603FT100K
R603: R_75K; R_0603; MPN RMCF0603FT75K0
TP601: TP_5V; TestPoint_Pad_D1.0mm
TP602: TP_12V; TestPoint_Pad_D1.0mm

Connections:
+5V: F602.2, TP601.1; also elsewhere on the board
+12V: F601.1, TP602.1; also elsewhere on the board
GND: C601.2, C602.2, C606.2, C607.2, D601.2 (A), IC601.6 (GND_1), IC601.9 (GND_2), R601.2, R603.2, R604.2; also elsewhere on the board
unnamed: C604.1, C606.1, C607.1, F602.1, L601.2, R602.1
unnamed: C603.2, D601.1 (K), IC601.8 (SW), L601.1
unnamed: C603.1, IC601.1 (BOOT)
unnamed: C604.2, IC601.4 (FB), R601.1, R602.2, R603.1, R604.1
unnamed: C601.1, C602.1, F601.2, IC601.7 (VIN)

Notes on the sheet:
Populating with an 82pF
R_2 = 31.5789kΩ

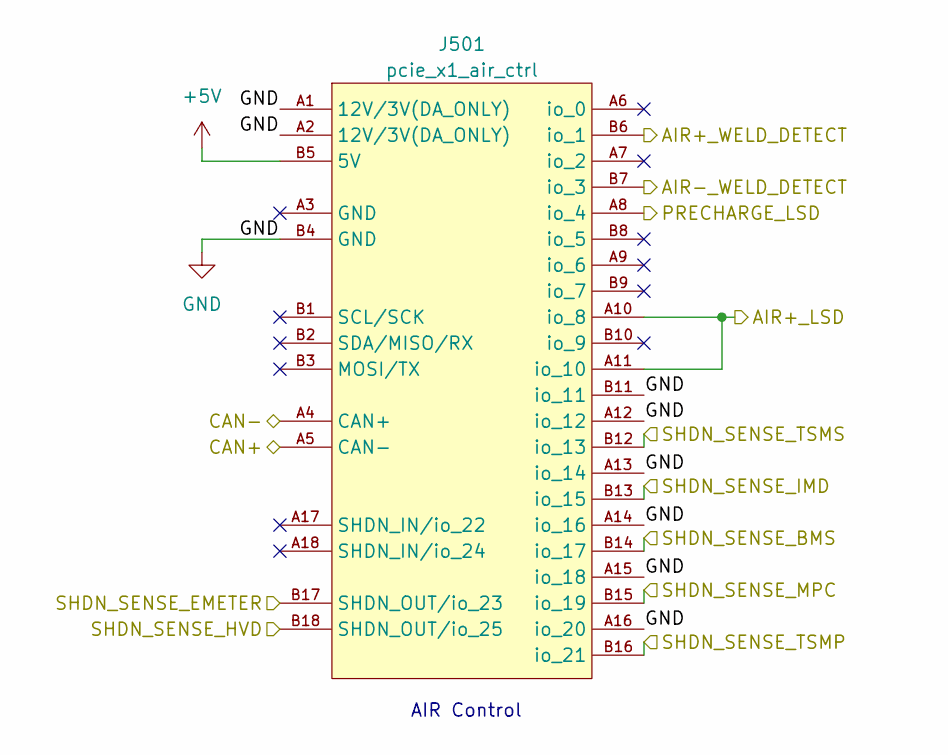
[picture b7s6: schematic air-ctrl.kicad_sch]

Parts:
J501: pcie_x1_air_ctrl; te_pcie_x1_connector

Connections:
+5V: J501.B5 (5V); also elsewhere on the board
/AIR+_LSD: J501.A10 (io_8), J501.A11 (io_10); also elsewhere on the board
/AIR+_WELD_DETECT: J501.B6 (io_1); also elsewhere on the board
/AIR-_WELD_DETECT: J501.B7 (io_3); also elsewhere on the board
/CAN+: J501.A5 (CAN-); also elsewhere on the board
/CAN-: J501.A4 (CAN+); also elsewhere on the board
/FINAL_SHDN: J501.B12 (io_13); also elsewhere on the board
/PRECHARGE_LSD: J501.A8 (io_4); also elsewhere on the board
/SHDN_SENSE_BMS: J501.B14 (io_17); also elsewhere on the board
/SHDN_SENSE_EMETER: J501.B17 (SHDN_OUT/io_23); also elsewhere on the board
/SHDN_SENSE_HVD: J501.B18 (SHDN_OUT/io_25); also elsewhere on the board
/SHDN_SENSE_IMD: J501.B13 (io_15); also elsewhere on the board
/SHDN_SENSE_MPC: J501.B15 (io_19); also elsewhere on the board
/SHDN_SENSE_TSMP: J501.B16 (io_21); also elsewhere on the board
GND: J501.A1 (12V/3V(DA_ONLY)), J501.A2 (12V/3V(DA_ONLY)), J501.A12 (io_12), J501.A13 (io_14), J501.A14 (io_16), J501.A15 (io_18), J501.A16 (io_20), J501.B4 (GND), J501.B11 (io_11); also elsewhere on the board

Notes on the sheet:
AIR Control
